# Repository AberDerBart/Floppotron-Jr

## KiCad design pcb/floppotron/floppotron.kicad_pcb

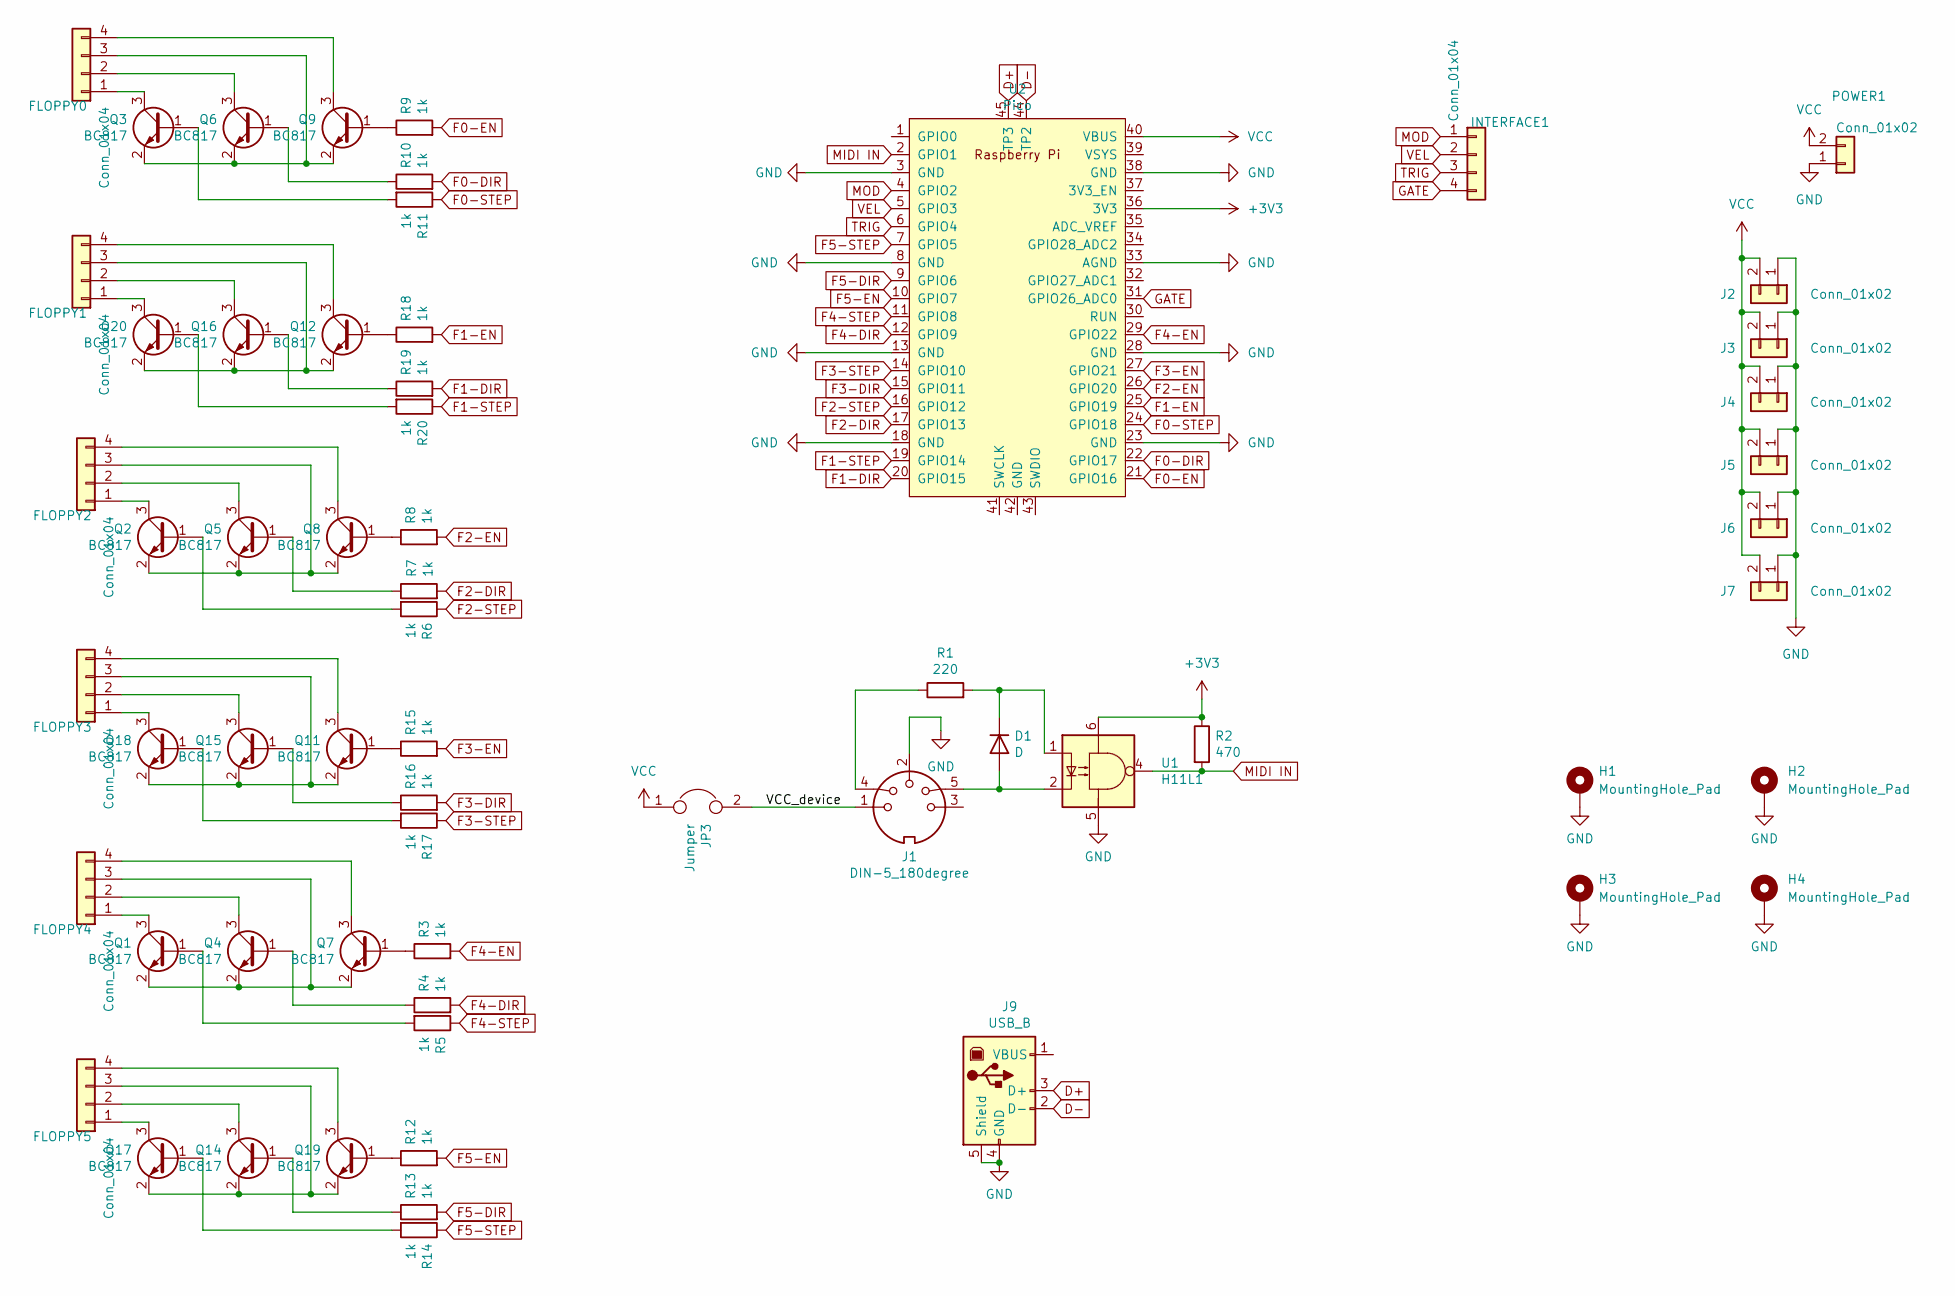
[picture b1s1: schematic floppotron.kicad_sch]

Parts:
D1: D; D_DO-34_SOD68_P7.62mm_Horizontal
FLOPPY0, FLOPPY1, FLOPPY2, FLOPPY3, FLOPPY4, FLOPPY5: Conn_01x04; JST_XH_B4B-XH-A_1x04_P2.50mm_Vertical
H1, H2, H3, H4: MountingHole_Pad; MountingHole_3.2mm_M3_DIN965_Pad
INTERFACE1: Conn_01x04; JST_XH_B4B-XH-A_1x04_P2.50mm_Vertical
J1: DIN-5_180degree; MIDI_DIN5
J2, J3, J4, J5, J6, J7: Conn_01x02; JST_XH_B2B-XH-A_1x02_P2.50mm_Vertical
J9: USB_B; USB_B_OST_USB-B1HSxx_Horizontal
JP3: Jumper; PinHeader_1x02_P2.54mm_Vertical
POWER1: Conn_01x02; TerminalBlock_bornier-2_P5.08mm
Q1, Q2, Q3, Q4, Q5, Q6, Q7, Q8, Q9, Q11, Q12, Q14, Q15, Q16, Q17, Q18, Q19, Q20: BC817; SOT-23_Handsoldering
R1: 220; R_1206_3216Metric_Pad1.30x1.75mm_HandSolder
R2: 470; R_1206_3216Metric_Pad1.30x1.75mm_HandSolder
R3, R4, R5, R6, R7, R8, R9, R10, R11, R12, R13, R14, R15, R16, R17, R18, R19, R20: 1k; R_1206_3216Metric_Pad1.30x1.75mm_HandSolder
U1: H11L1; DIP-6_W7.62mm_Socket
U2: Pico; RPi_Pico_debug_hole_USB_SMD_TH

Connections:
+3V3: R2.1, U1.6, U2.36 (3V3)
/VCC_device: J1.1, JP3.2
D+: J9.3 (D+), U2.45 (TP3)
D-: J9.2 (D-), U2.44 (TP2)
F0-DIR: R10.2, U2.22 (GPIO17)
F0-EN: R9.2, U2.21 (GPIO16)
F0-STEP: R11.1, U2.24 (GPIO18)
F1-DIR: R19.2, U2.20 (GPIO15)
F1-EN: R18.2, U2.25 (GPIO19)
F1-STEP: R20.1, U2.19 (GPIO14)
F2-DIR: R7.2, U2.17 (GPIO13)
F2-EN: R8.2, U2.26 (GPIO20)
F2-STEP: R6.1, U2.16 (GPIO12)
F3-DIR: R16.2, U2.15 (GPIO11)
F3-EN: R15.2, U2.27 (GPIO21)
F3-STEP: R17.1, U2.14 (GPIO10)
F4-DIR: R4.2, U2.12 (GPIO9)
F4-EN: R3.2, U2.29 (GPIO22)
F4-STEP: R5.1, U2.11 (GPIO8)
F5-DIR: R13.2, U2.9 (GPIO6)
F5-EN: R12.2, U2.10 (GPIO7)
F5-STEP: R14.1, U2.7 (GPIO5)
GATE: INTERFACE1.4, U2.31 (GPIO26_ADC0); also elsewhere on the board
GND: H1.1, H2.1, H3.1, H4.1, J1.2, J2.1, J3.1, J4.1, J5.1, J6.1, J7.1, J9.4 (GND), J9.5 (Shield), POWER1.1, U1.5, U2.3 (GND), U2.8 (GND), U2.13 (GND), U2.18 (GND), U2.23 (GND), U2.28 (GND), U2.33 (AGND), U2.38 (GND)
MIDI IN: R2.2, U1.4, U2.2 (GPIO1)
MOD: INTERFACE1.1, U2.4 (GPIO2); also elsewhere on the board
unnamed: D1.2 (A), J1.5, U1.2
unnamed: D1.1 (K), R1.2, U1.1
unnamed: FLOPPY0.1, Q3.3 (C)
unnamed: FLOPPY0.2, Q6.3 (C)
unnamed: FLOPPY0.3, Q3.2 (E), Q6.2 (E), Q9.2 (E)
unnamed: FLOPPY0.4, Q9.3 (C)
unnamed: FLOPPY1.1, Q20.3 (C)
unnamed: FLOPPY1.2, Q16.3 (C)
unnamed: FLOPPY1.3, Q12.2 (E), Q16.2 (E), Q20.2 (E)
unnamed: FLOPPY1.4, Q12.3 (C)
unnamed: FLOPPY2.1, Q2.3 (C)
unnamed: FLOPPY2.2, Q5.3 (C)
unnamed: FLOPPY2.3, Q2.2 (E), Q5.2 (E), Q8.2 (E)
unnamed: FLOPPY2.4, Q8.3 (C)
unnamed: FLOPPY3.1, Q18.3 (C)
unnamed: FLOPPY3.2, Q15.3 (C)
unnamed: FLOPPY3.3, Q11.2 (E), Q15.2 (E), Q18.2 (E)
unnamed: FLOPPY3.4, Q11.3 (C)
unnamed: FLOPPY4.1, Q1.3 (C)
unnamed: FLOPPY4.2, Q4.3 (C)
unnamed: FLOPPY4.3, Q1.2 (E), Q4.2 (E), Q7.2 (E)
unnamed: FLOPPY4.4, Q7.3 (C)
unnamed: FLOPPY5.1, Q17.3 (C)
unnamed: FLOPPY5.2, Q14.3 (C)
unnamed: FLOPPY5.3, Q14.2 (E), Q17.2 (E), Q19.2 (E)
unnamed: FLOPPY5.4, Q19.3 (C)
unnamed: J1.4, R1.1
unnamed: Q1.1 (B), R5.2
unnamed: Q2.1 (B), R6.2
unnamed: Q3.1 (B), R11.2
unnamed: Q4.1 (B), R4.1
unnamed: Q5.1 (B), R7.1
unnamed: Q6.1 (B), R10.1
unnamed: Q7.1 (B), R3.1
unnamed: Q8.1 (B), R8.1
unnamed: Q9.1 (B), R9.1
unnamed: Q11.1 (B), R15.1
unnamed: Q12.1 (B), R18.1
unnamed: Q14.1 (B), R13.1
unnamed: Q15.1 (B), R16.1
unnamed: Q16.1 (B), R19.1
unnamed: Q17.1 (B), R14.2
unnamed: Q18.1 (B), R17.2
unnamed: Q19.1 (B), R12.1
unnamed: Q20.1 (B), R20.2
TRIG: INTERFACE1.3, U2.6 (GPIO4); also elsewhere on the board
VCC: J2.2, J3.2, J4.2, J5.2, J6.2, J7.2, JP3.1, POWER1.2, U2.40 (VBUS)
VEL: INTERFACE1.2, U2.5 (GPIO3); also elsewhere on the board

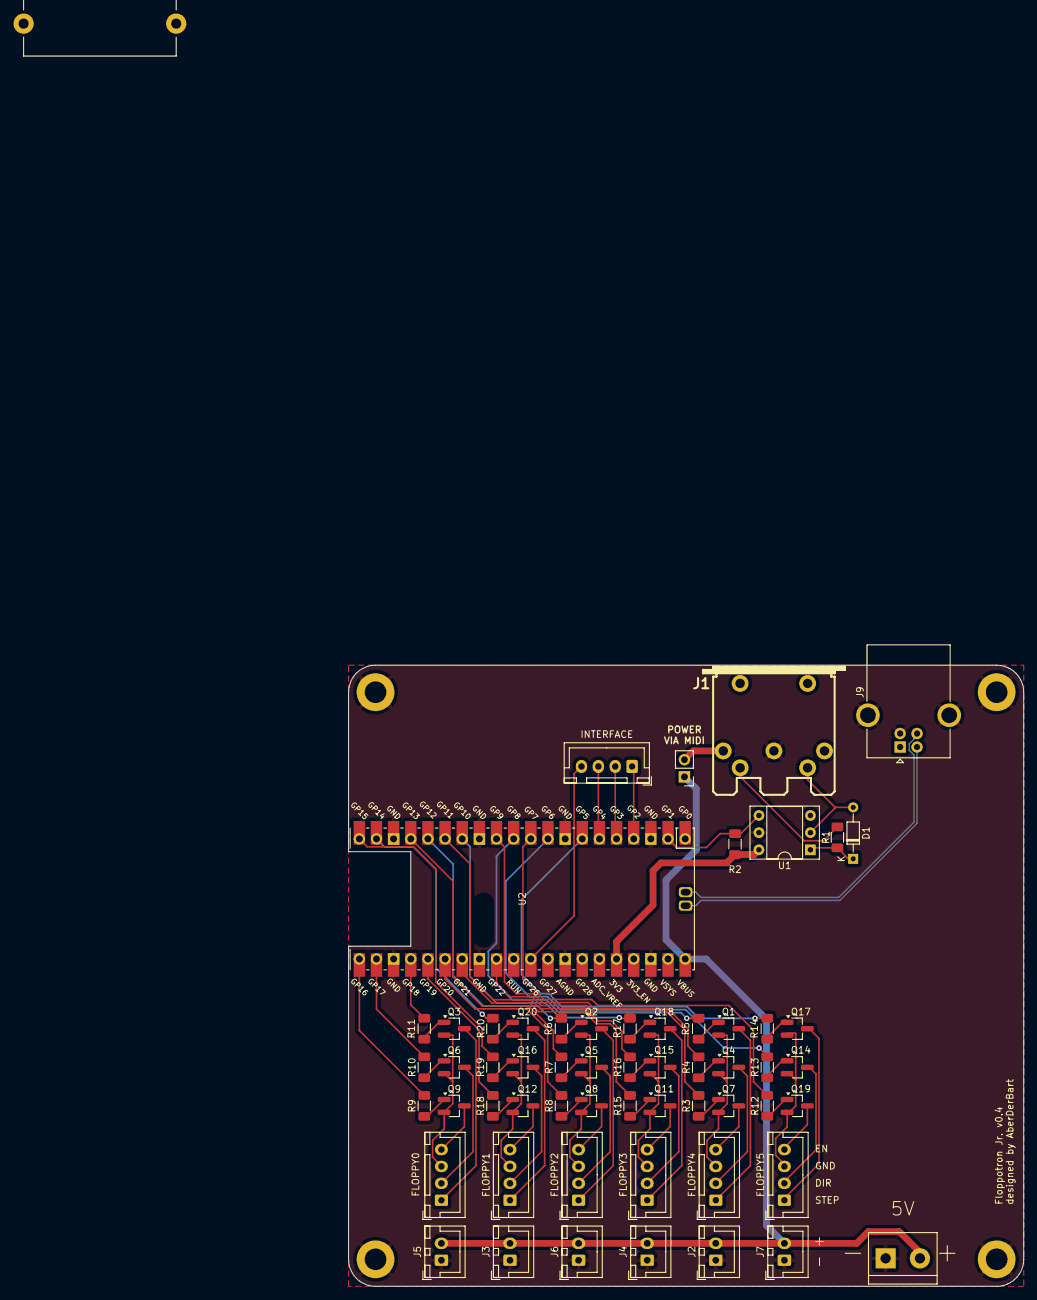
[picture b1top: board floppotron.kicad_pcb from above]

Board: 2 copper layers, 100.0 x 92.0 mm, 63 parts (0 on the bottom side), 74 nets.

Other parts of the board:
F1: Fuse; Fuseholder_Cylinder-5x20mm_Stelvio-Kontek_PTF78_Horizontal_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
INTERFACE: Conn_01x04; JST_XH_B4B-XH-A_1x04_P2.50mm_Vertical

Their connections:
GATE: INTERFACE.4; also elsewhere on the board
MOD: INTERFACE.1; also elsewhere on the board
TRIG: INTERFACE.3; also elsewhere on the board
VEL: INTERFACE.2; also elsewhere on the board

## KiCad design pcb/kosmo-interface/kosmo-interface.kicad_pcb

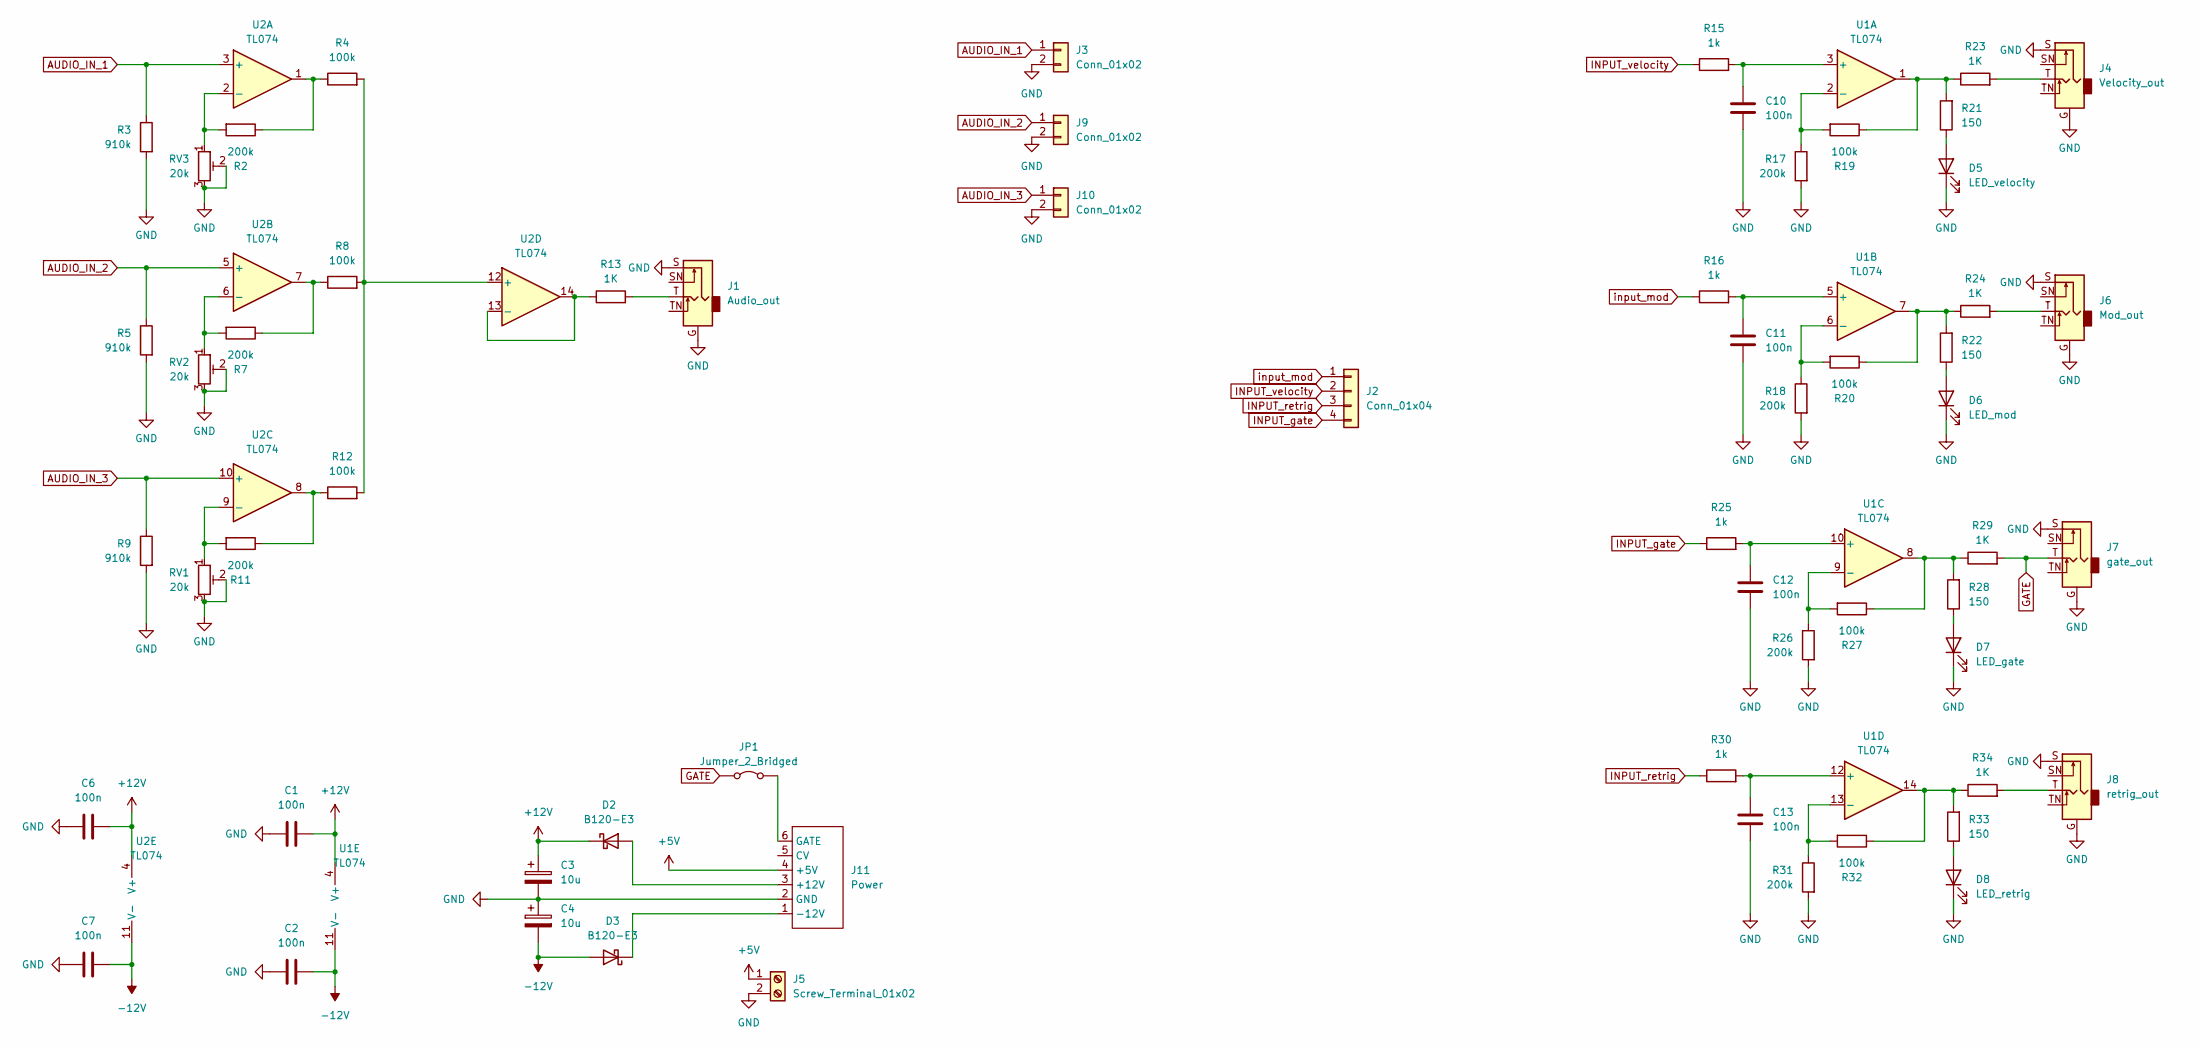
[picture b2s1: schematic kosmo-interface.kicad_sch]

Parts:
C1, C2, C6, C7, C10, C11, C12, C13: 100n; C_1206_3216Metric_Pad1.33x1.80mm_HandSolder
C3, C4: 10u; CP_Radial_D8.0mm_P3.50mm
D2, D3: B120-E3; D_SMA
D5: LED_velocity; LED_5mm_side_centered
D6: LED_mod; LED_5mm_side_centered
D7: LED_gate; LED_5mm_side_centered
D8: LED_retrig; LED_5mm_side_centered
J1: Audio_out; jack-neutrik-horizontal
J2: Conn_01x04; JST_XH_B4B-XH-A_1x04_P2.50mm_Vertical
J3, J9, J10: Conn_01x02; JST_XH_B2B-XH-A_1x02_P2.50mm_Vertical
J4: Velocity_out; jack-neutrik-horizontal
J5: Screw_Terminal_01x02; TerminalBlock_MetzConnect_Type055_RT01502HDWU_1x02_P5.00mm_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
J6: Mod_out; jack-neutrik-horizontal
J7: gate_out; jack-neutrik-horizontal
J8: retrig_out; jack-neutrik-horizontal
J11: Power; Power 16 Pin
JP1: Jumper_2_Bridged; SolderJumper-2_P1.3mm_Open_RoundedPad1.0x1.5mm
R2, R7, R11, R17, R18, R26, R31: 200k; R_1206_3216Metric_Pad1.30x1.75mm_HandSolder
R3, R5, R9: 910k; R_1206_3216Metric_Pad1.30x1.75mm_HandSolder
R4, R8, R12, R19, R20, R27, R32: 100k; R_1206_3216Metric_Pad1.30x1.75mm_HandSolder
R13, R23, R24, R29, R34: 1K; R_1206_3216Metric_Pad1.30x1.75mm_HandSolder
R15, R16, R25, R30: 1k; R_1206_3216Metric_Pad1.30x1.75mm_HandSolder
R21, R22, R28, R33: 150; R_1206_3216Metric_Pad1.30x1.75mm_HandSolder
RV1, RV2, RV3: 20k; Potentiometer_Bourns_3296W_Vertical
U1: TL074; DIP-14_W7.62mm
U2: TL074

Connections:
+5V: J5.1, J11.4 (+5V)
+12V: C1.2, C3.1, C6.2, D2.1 (K), U1.4 (V+), U2.4 (V+)
-12V: C2.2, C4.2, C7.2, D3.2 (A), U1.11 (V-), U2.11 (V-)
AUDIO_IN_1: J3.1, R3.1, U2.3 (+)
AUDIO_IN_2: J9.1, R5.1, U2.5 (+)
AUDIO_IN_3: J10.1, R9.1, U2.10 (+)
GATE: J7.T, JP1.1 (A), R29.2
GND: C1.1, C2.1, C3.2, C4.1, C6.1, C7.1, C10.2, C11.2, C12.2, C13.2, D5.1 (K), D6.1 (K), D7.1 (K), D8.1 (K), J1.G, J1.S, J3.2, J4.G, J4.S, J5.2, J6.G, J6.S, J7.G, J7.S, J8.G, J8.S, J9.2, J10.2, J11.2 (GND), R3.2, R5.2, R9.2, R17.2, R18.2, R26.2, R31.2, RV1.2, RV1.3, RV2.2, RV2.3, RV3.2, RV3.3
INPUT_gate: J2.4, R25.1
INPUT_retrig: J2.3, R30.1
INPUT_velocity: J2.2, R15.1
unnamed: D2.2 (A), J11.3 (+12V)
unnamed: D3.1 (K), J11.1 (-12V)
unnamed: D5.2 (A), R21.1
unnamed: D6.2 (A), R22.1
unnamed: D7.2 (A), R28.1
unnamed: D8.2 (A), R33.1
unnamed: J1.T, R13.2
unnamed: J4.T, R23.2
unnamed: J6.T, R24.2
unnamed: J8.T, R34.2
unnamed: J11.6 (GATE), JP1.2 (B)
unnamed: R2.1, R4.1, U2.1
unnamed: R7.1, R8.1, U2.7
unnamed: R11.1, R12.1, U2.8
unnamed: R19.1, R21.2, R23.1, U1.1
unnamed: R20.1, R22.2, R24.1, U1.7
unnamed: R27.1, R28.2, R29.1, U1.8
unnamed: R32.1, R33.2, R34.1, U1.14
unnamed: C10.1, R15.2, U1.3 (+)
unnamed: R17.1, R19.2, U1.2 (-)
unnamed: C11.1, R16.2, U1.5 (+)
unnamed: R18.1, R20.2, U1.6 (-)
unnamed: C12.1, R25.2, U1.10 (+)
unnamed: R26.1, R27.2, U1.9 (-)
unnamed: C13.1, R30.2, U1.12 (+)
unnamed: R31.1, R32.2, U1.13 (-)
unnamed: R2.2, RV3.1, U2.2 (-)
unnamed: R7.2, RV2.1, U2.6 (-)
unnamed: R11.2, RV1.1, U2.9 (-)
unnamed: R4.2, R8.2, R12.2, U2.12 (+)
unnamed: R13.1, U2.13 (-), U2.14
input_mod: J2.1, R16.1

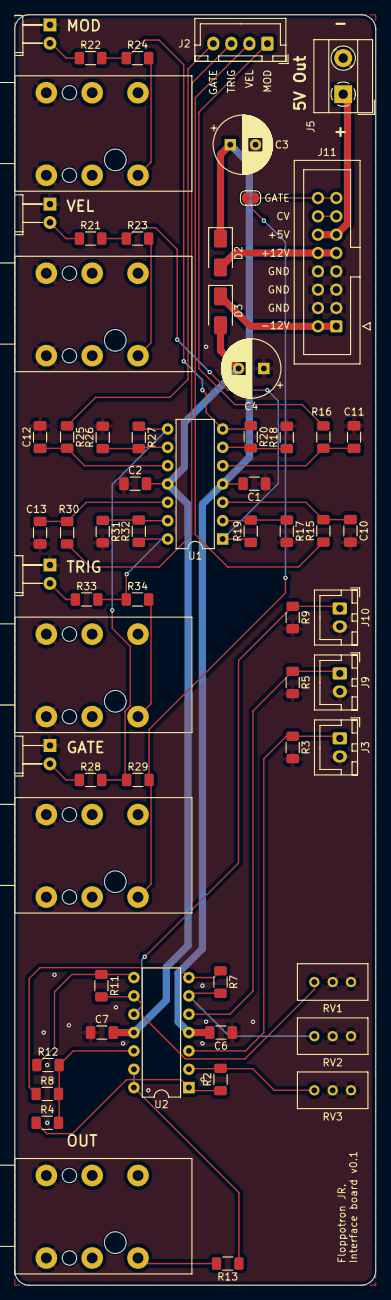
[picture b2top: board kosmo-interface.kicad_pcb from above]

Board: 2 copper layers, 50.0 x 176.0 mm, 63 parts (0 on the bottom side), 43 nets.

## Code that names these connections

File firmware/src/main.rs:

//! Blinks the LED on a Pico board
//!
//! This will blink an LED attached to GP25, which is the pin the Pico uses for the on-board LED.
#![no_std]
#![no_main]

use core::ops::DerefMut;

use bsp::entry;
use cortex_m::interrupt;
use defmt::*;
use defmt_rtt as _;
use panic_probe as _;

use floppotron_jr::{
    deactivate_slice_ints,
    floppy::{Floppy0, Floppy1, Floppy2, Floppy3, Floppy4, Floppy5},
    listen_to_midi,
    oscillators::{OscConfiguration, OSCILLATORS},
};
// Provide an alias for our BSP so we can switch targets quickly.
// Uncomment the BSP you included in Cargo.toml, the rest of the code does not need to change.
use rp_pico as bsp;
// use sparkfun_pro_micro_rp2040 as bsp;

use bsp::hal::{
    clocks::{init_clocks_and_plls, Clock},
    pac,
    sio::Sio,
    watchdog::Watchdog,
};

#[entry]
fn main() -> ! {
    info!("Program start");
    let mut pac = pac::Peripherals::take().unwrap();
    let mut watchdog = Watchdog::new(pac.WATCHDOG);
    let sio = Sio::new(pac.SIO);

    // External high-speed crystal on the pico board is 12Mhz
    let external_xtal_freq_hz = 12_000_000u32;
    let clocks = init_clocks_and_plls(
        external_xtal_freq_hz,
        pac.XOSC,
        pac.CLOCKS,
        pac.PLL_SYS,
        pac.PLL_USB,
        &mut pac.RESETS,
        &mut watchdog,
    )
    .ok()
    .unwrap();
    let pins = bsp::Pins::new(
        pac.IO_BANK0,
        pac.PADS_BANK0,
        sio.gpio_bank0,
        &mut pac.RESETS,
    );

    let mut slices = bsp::hal::pwm::Slices::new(pac.PWM, &mut pac.RESETS);

    slices.pwm0.set_div_int(255);
    slices.pwm0.set_top(65465);
    slices.pwm0.enable();

    // let step_pin = pins.gpio26.into_push_pull_output();
    // let dir_pin = pins.gpio27.into_push_pull_output();
    // let en_pin = pins.gpio28.into_push_pull_output();

    let floppy0 = Floppy0::new(
        pins.gpio26.into_push_pull_output(),
        pins.gpio27.into_push_pull_output(),
        pins.gpio28.into_push_pull_output(),
    );

    let floppy1 = Floppy1::new(
        pins.gpio7.into_push_pull_output(),
        pins.gpio6.into_push_pull_output(),
        pins.gpio5.into_push_pull_output(),
    );

    let floppy2 = Floppy2::new(
        pins.gpio20.into_push_pull_output(),
        pins.gpio21.into_push_pull_output(),
        pins.gpio22.into_push_pull_output(),
    );

    let floppy3 = Floppy3::new(
        pins.gpio11.into_push_pull_output(),
        pins.gpio10.into_push_pull_output(),
        pins.gpio9.into_push_pull_output(),
    );

    let floppy4 = Floppy4::new(
        pins.gpio16.into_push_pull_output(),
        pins.gpio17.into_push_pull_output(),
        pins.gpio18.into_push_pull_output(),
    );

    let floppy5 = Floppy5::new(
        pins.gpio15.into_push_pull_output(),
        pins.gpio14.into_push_pull_output(),
        pins.gpio13.into_push_pull_output(),
    );

    let floppies = (floppy0, floppy1, floppy2, floppy3, floppy4, floppy5);

    deactivate_slice_ints(&mut slices);

    let slices = (
        slices.pwm0,
        slices.pwm1,
        slices.pwm2,
        slices.pwm3,
        slices.pwm4,
        slices.pwm5,
    );

    info!("unmasked");

    let osc_config = OscConfiguration::new_single(slices, floppies);
    info!("config initialized");

    interrupt::free(|cs| {
        OSCILLATORS
            .borrow(cs)
            .borrow_mut()
            .deref_mut()
            .init_with_config(osc_config)
    });

    let uart_pins = (
        pins.gpio0.into_mode::<bsp::hal::gpio::FunctionUart>(),
        pins.gpio1.into_mode::<bsp::hal::gpio::FunctionUart>(),
    );
    let uart0 = bsp::hal::uart::UartPeripheral::new(pac.UART0, uart_pins, &mut pac.RESETS);

    info!("freq: {}", clocks.peripheral_clock.freq().0,);

    let led_pin = pins.led.into_push_pull_output();

    // enable PWM interrupt
    unsafe {
        info!("unmask");
        pac::NVIC::unmask(pac::Interrupt::PWM_IRQ_WRAP); // infinite loop?
        info!("enable");
        interrupt::enable(); // infinite loop?
    }

    listen_to_midi(uart0, led_pin);
}

// End of file

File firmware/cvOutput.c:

#include "cvOutput.h"

#include <stdbool.h>

#include "hardware/pwm.h"
#include "oscillator.h"
#include "pico/stdlib.h"

#define VELOCITY_PIN 2
#define MOD_PIN 3

#define GATE_PIN 26
#define TRIG_PIN 4

#define A_OUT_PWM_SLICE 1

#define VELOCITY_CHAN PWM_CHAN_B
#define MOD_CHAN PWM_CHAN_A

#define TRIG_ALARM_NUM 0
#define TRIG_DURATION_US 5000

static void reset_trig() { gpio_put(TRIG_PIN, false); }

void cv_output_init() {
  gpio_init(GATE_PIN);
  gpio_set_dir(GATE_PIN, true);

  gpio_init(TRIG_PIN);
  gpio_set_dir(TRIG_PIN, true);

  // init PWM for velocity and mod
  pwm_set_irq_enabled(A_OUT_PWM_SLICE, false);
  pwm_set_wrap(A_OUT_PWM_SLICE, 127);

  set_velocity(0);
  set_mod(0);

  gpio_set_function(VELOCITY_PIN, GPIO_FUNC_PWM);
  gpio_set_function(MOD_PIN, GPIO_FUNC_PWM);

  pwm_set_enabled(A_OUT_PWM_SLICE, true);

  // init alarm for turning off trigger signal
  hardware_alarm_claim(TRIG_ALARM_NUM);
  hardware_alarm_set_callback(TRIG_ALARM_NUM, reset_trig);
}

void set_velocity(uint8_t velocity) {
  pwm_set_chan_level(A_OUT_PWM_SLICE, VELOCITY_CHAN, velocity);
}

void set_mod(uint8_t mod) {
  pwm_set_chan_level(A_OUT_PWM_SLICE, MOD_CHAN, mod);
}

void pulse_trig() {
  absolute_time_t current_time = time_us_64();
  hardware_alarm_set_target(TRIG_ALARM_NUM, current_time + TRIG_DURATION_US);
  gpio_put(TRIG_PIN, true);
}

void set_gate(bool gate) { gpio_put(GATE_PIN, gate); }

void set_velocity_u32(uint32_t velocity) {
  pwm_set_chan_level(A_OUT_PWM_SLICE, VELOCITY_CHAN, velocity >> (32 - 7));
}

void cv_output_task() { set_velocity_u32(oscillators_get_level()); }

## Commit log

2022-03-25 implement inverse oscillator
2022-03-25 implement oscillator configuration switching
2022-03-25 stop oscillators before freeing them
2022-03-25 generalize calling functions on all oscillators
2022-03-28 implement note stack
2022-11-05 add case
2022-11-05 add piezos to case
2022-11-09 change toolchain
2022-11-09 fix firmware
2022-11-09 adjust workspace
2022-11-09 ignore stl and 3mf files
2022-11-09 add pcb
2022-11-11 firmware: fix build
2022-11-11 firmware: notedict: remove debug prints
2024-05-14 redesign pcb for pico W
2024-05-14 clean up case code
2024-05-14 pcb: add kosmo power connector
2024-05-14 clean up traces
2024-12-11 pcb: add interface board
2024-12-11 pcb: adapt for interface board
2024-12-11 case: adapt for kosmo interface
2024-12-12 case: add labels
2024-12-16 add c firmware
    for future BLE midi compatibility
2024-12-18 firmware-c: refactoring and formatting
2024-12-18 firmware-c: consistently use pwm slice from oscillator struct
    instead of using index sometimes.
    this allows to decouple the oscillators indices from the slice indices
2024-12-18 firmware-c: re-assign oscillator pwm slices
2024-12-18 firmware-c: add CV output
2024-12-18 firmware-c: implement gate signal
2024-12-18 firmware-c: implement trig signal
2024-12-18 firmware-c: implement all notes off CC command
2024-12-18 firmware-c: implement modulation wheel CC
2024-12-18 firmware-c: use switch/case for midi statu
2024-12-18 firmware-c: implement velocity output
2024-12-22 remove unneeded dependencies
2025-01-03 firmware-c: fix overflow in pitchbend/note offset calculation
2025-01-03 firmware-c: add BLE support
2025-01-03 firmware-c: handle ble midi packages
2025-01-03 flake.nix: add testing tools and libraries
2025-03-10 firmware-c: inititalize floppy head position on powerup
2025-03-10 firmware-c: format code
2025-03-10 wip: implement envelopes
2025-04-28 firmware-c: implement envelopes
2025-04-28 fix retrigger not working for notes during release
2025-04-28 fixup! fix retrigger not working for notes during release
2025-04-28 firmware-c: reduce ripple on cv outputs
2025-08-07 firmware-c: set envelope via midi CC
2025-08-07 remove firmware (rust)
2025-08-07 rename firmware-c to firmware
